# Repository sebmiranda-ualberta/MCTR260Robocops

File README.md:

# MCTR 260 Robocops
The GitHub repository for the Robocops! We are Group 10 in the MCTR 260 course on Mechatronics Design at the University of Alberta.

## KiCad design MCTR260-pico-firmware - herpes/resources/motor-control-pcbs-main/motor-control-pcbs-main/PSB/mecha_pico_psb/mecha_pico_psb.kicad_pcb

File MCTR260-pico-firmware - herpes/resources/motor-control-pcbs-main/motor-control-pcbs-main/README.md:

# MechaPico

This repository contains the KiCad project files
and component datasheets for the MechaPico Motor Control Board (MCB),
and Power Supply Board (PSB); developed by Stephine Yearley under
the guidance of Dr. Steven Knudsen at the University of Alberta.

TODO - Flesh out the README as development progresses

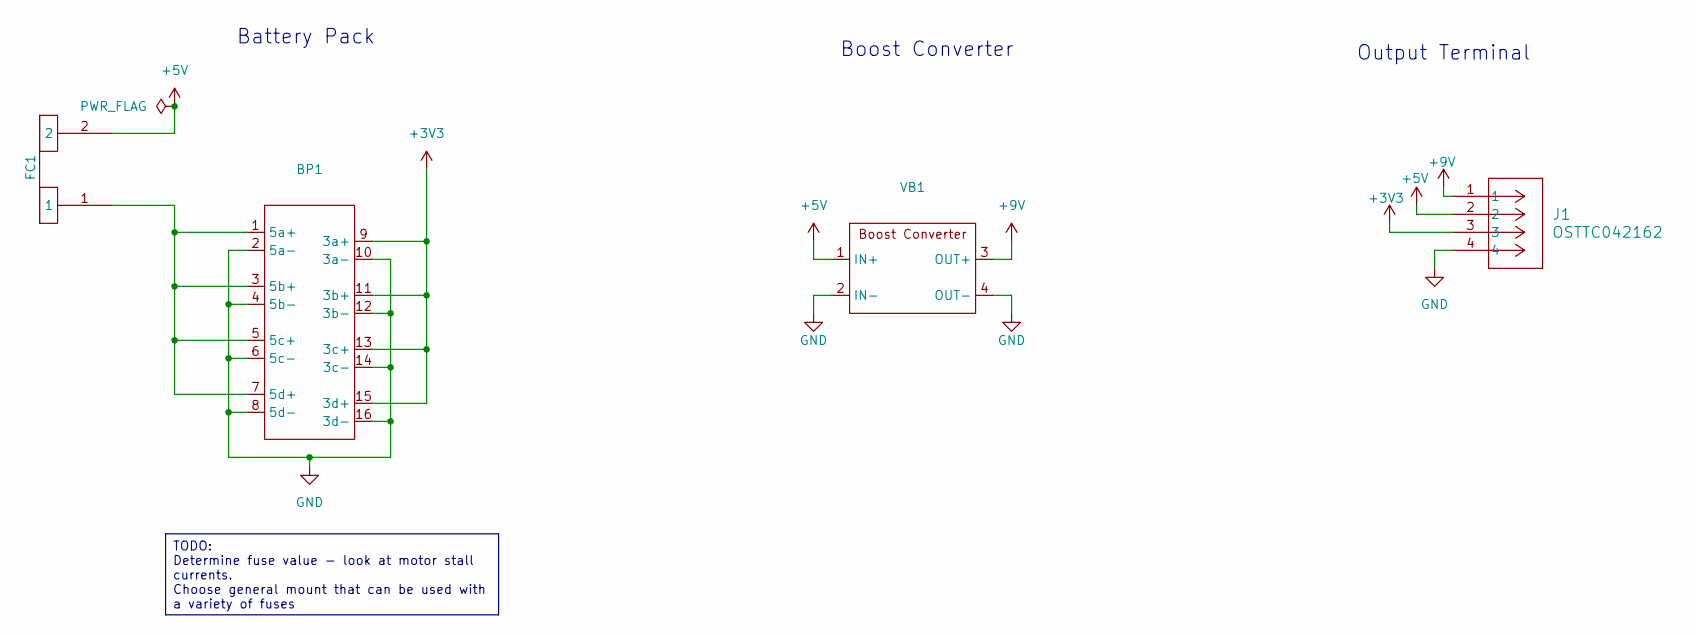
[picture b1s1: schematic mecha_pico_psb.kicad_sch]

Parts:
BP1: DIYmore_BatPak
FC1: FuseClip
J1: OSTTC042162; CONN_OSTTC042162_OST
VB1: VoltageBooster

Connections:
+3V3: BP1.9 (3a+), BP1.11 (3b+), BP1.13 (3c+), BP1.15 (3d+), J1.3
+5V: FC1.2, J1.2, VB1.1 (IN+)
+9V: J1.1, VB1.3 (OUT+)
GND: BP1.2 (5a-), BP1.4 (5b-), BP1.6 (5c-), BP1.8 (5d-), BP1.10 (3a-), BP1.12 (3b-), BP1.14 (3c-), BP1.16 (3d-), J1.4, VB1.2 (IN-), VB1.4 (OUT-)
unnamed: BP1.1 (5a+), BP1.3 (5b+), BP1.5 (5c+), BP1.7 (5d+), FC1.1

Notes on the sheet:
Output Terminal
Battery Pack
Boost Converter
TODO: Determine fuse value - look at motor stall currents. Choose general mount that can be used with a variety of fuses

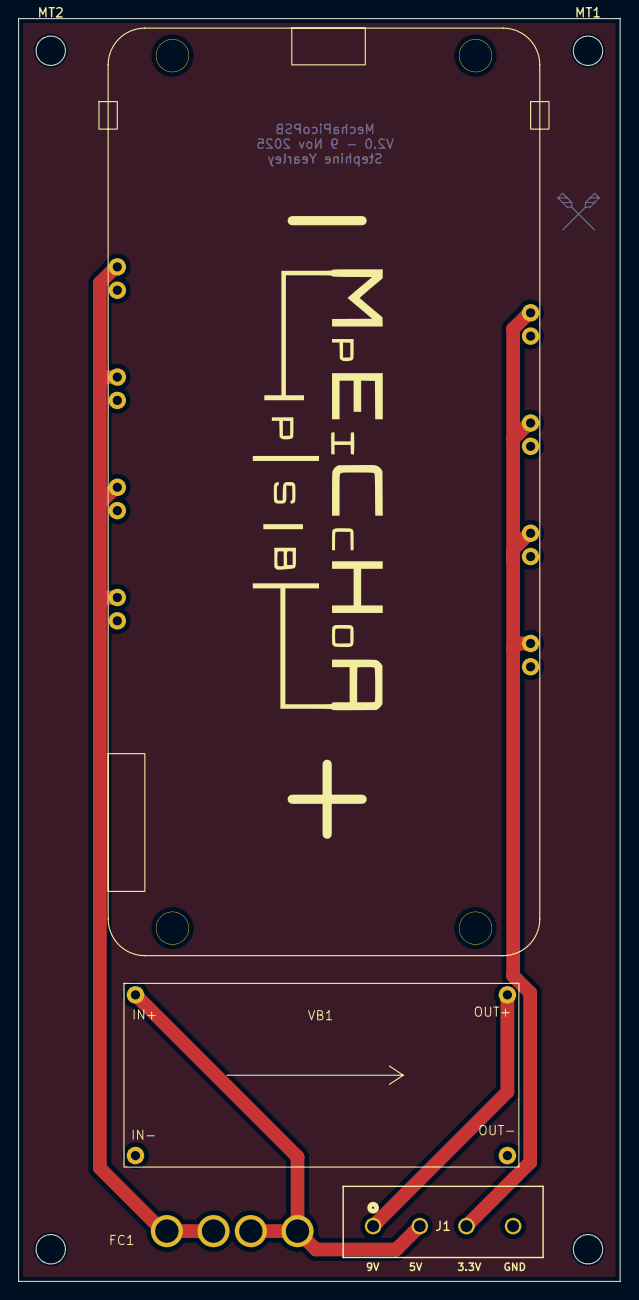
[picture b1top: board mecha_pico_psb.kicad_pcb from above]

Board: 2 copper layers, 65.5 x 137.5 mm, 8 parts (0 on the bottom side), 5 nets.

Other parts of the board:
MT1, MT2, MT3, MT4: MountingHole_3.2mm_M3

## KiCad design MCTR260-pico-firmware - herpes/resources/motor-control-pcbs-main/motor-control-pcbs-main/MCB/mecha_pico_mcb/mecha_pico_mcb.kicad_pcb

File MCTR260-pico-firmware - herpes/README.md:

# Raspberry Pi Pico W Robot Firmware

## What This Firmware Does

This firmware turns a Raspberry Pi Pico W into a **wireless robot controller**. You connect to it with a phone app over Bluetooth, and it translates your joystick movements into motor commands. It supports both DC motors (like the ones in toy cars) and stepper motors (precise motors that move in discrete steps), and it handles all the real-time control, safety, and communication automatically.

**In one sentence:** Phone app → Bluetooth → Pico W → motor drivers → wheels spin.

> [!IMPORTANT]
> **Hardware Platform:** This project is built around the **MECHA PICO** expansion board, a custom PCB designed for the MCTR 260 term project at the University of Alberta. All documentation, pin assignments, wiring diagrams, and code examples assume this specific board. If you are building from a bare Pico W, refer to the [Wiring Guide](doc/user_guide_documentation/WIRING_GUIDE.md) for the full connection list.

---

## How It Works

When you push the joystick in the Flutter app, here is what happens:

1. **App sends a JSON command** over Bluetooth Low Energy (BLE) to the Pico W
2. **Pico W parses the JSON** and extracts joystick position (x, y, rotation)
3. **Kinematics math runs** to convert your joystick input into 4 individual wheel speeds
4. **Motor drivers receive signals** (PWM for DC motors, step pulses for steppers)
5. **Safety watchdog monitors** the connection and stops everything if your phone disconnects

The Pico W has **two processor cores**. Core 0 handles Bluetooth and decision-making. Core 1 handles real-time stepper motor pulses. This separation ensures that Bluetooth processing never causes motor stuttering, and motor timing never blocks your Bluetooth connection.

---

## What You Need

### Hardware

| Component | Purpose | Notes |
|-----------|---------|-------|
| Raspberry Pi Pico W | The microcontroller brain | Must be the **W** variant (has Bluetooth) |
| Motor driver board(s) | Converts logic signals to motor power | See [Supported Motor Drivers](#supported-motor-drivers) below |
| Motors (up to 5 stepper + 2 DC) | Stepper and/or DC, depending on your build | Drive motors should be the same type |
| Power supply | Battery or bench supply | Voltage depends on your motors |
| USB cable | For uploading firmware and serial debugging | Micro-USB for Pico W |

### Software

| Tool | Purpose | Where to Get It |
|------|---------|-----------------|
| VS Code | Code editor | [code.visualstudio.com](https://code.visualstudio.com/) |
| PlatformIO extension | Builds and uploads firmware | Install from VS Code Extensions tab |
| RC Controller app | Phone app to drive the robot | Provided separately (Flutter) |

---

## Quick Start

> [!TIP]
> If this is your first time, read [GETTING_STARTED.md](doc/user_guide_documentation/GETTING_STARTED.md) for a detailed walkthrough of every step.

1. Open this project folder in VS Code with PlatformIO installed
2. Edit `src/project_config.h` to set your robot's name, PIN, and motor driver type
3. Build and upload:
   ```
   pio run -t upload
   ```
4. Open serial monitor to verify boot:
   ```
   pio run -t monitor
   ```
5. Open the Flutter app → scan for your robot → enter the PIN → drive!

---

## Project Structure

```
├── platformio.ini          # Build configuration (do not edit unless adding libraries)
├── src/
│   ├── project_config.h    # ← YOUR SETTINGS (device name, PIN, motor type, GPIO pins)
│   ├── main.cpp            # Entry point for both cores
│   ├── core/               # BLE communication, command parsing, motor management, safety
│   ├── drivers/            # Hardware drivers (MCP23017, kinematics math)
│   └── profiles/           # Motion profiles (mecanum, auxiliary motors)
├── doc/                    # Student documentation
├── resources/              # PCB design files and datasheets
├── LICENSE                 # MIT License
└── README.md               # You are here
```

**Key file:** `src/project_config.h` is the **only file** you need to edit for basic setup. Everything else is internal firmware code.

---

## Supported Motor Drivers

### DC Motor Drivers

| Driver | Motors per Chip | Pico Pins per Motor | Max Current | Best For |
|--------|:--------------:|:-------------------:|:-----------:|----------|
| DRV8871 | 1 | 2 PWM | 3.6A | High-power single motors |
| DRV8833 | 2 | 2 PWM | 1.5A | Small to medium robots |
| L298N | 2 | 3 (2 dir + 1 PWM) | 2A | Easy to source, common in kits |

### Stepper Motor Drivers

| Driver | Max Microsteps | Max Current | Noise Level | Best For |
|--------|:--------------:|:-----------:|:-----------:|----------|
| TMC2209 | 1/256 (internal) | 2.8A | Very quiet | Precision, quiet operation |
| A4988 | 1/16 | 2A | Moderate | Budget builds |
| DRV8825 | 1/32 | 2.5A | Moderate | Mid-range, higher resolution |

> [!IMPORTANT]
> You must uncomment **exactly one** motor driver in `project_config.h`. Uncommenting more than one causes a compile error.

### Which Driver Should I Pick?

- **Using the MechaPico MCB (custom PCB)?** → Use `TMC2209` (it is pre-wired on the board)
- **Building from scratch with DC motors?** → Start with `DRV8833` (cheap, 2 motors per chip)
- **Need maximum torque?** → Use `DRV8871` (highest current per channel)
- **Using stepper motors on a breadboard?** → Start with `A4988` (widely available, simple wiring)

---

## BLE Pairing

1. Power on your robot (plug in USB or connect battery)
2. Open the Flutter RC Controller app
3. Tap **Scan** on the connection screen
4. Select your robot's name from the list (e.g., `TimberBot_RC`)
5. Enter the 6-digit PIN (default: `123456`, set in `project_config.h`)
6. You are connected. Push the joystick to drive.

> [!TIP]
> **Robot not appearing in the scan list?** Include one of these keywords in your device name so the app shows it at the top: `robot`, `rc`, `pico`, `mecanum`, `tank`, `meca`, `controller`.

> [!WARNING]
> If you change `DEVICE_NAME` or `BLE_PASSKEY` in the firmware, your phone will see a "new device." Delete the old pairing from your phone's Bluetooth settings and re-pair.

---

## Feature Status

| Feature | Status | Notes |
|---------|:------:|-------|
| BLE Control | ✅ | BTstack GATT server with passkey pairing |
| DC Motors (M1-M4) | ✅ | DRV8871, DRV8833, L298N drivers via Pico GPIO |
| Stepper Motors (M1-M4) | ✅ | TMC2209, A4988, DRV8825 via MCP23017 |
| Motor 5 (Spare Stepper) | ✅ | Config-only: runs on Core 1 with full acceleration |
| DC Motors 3-4 (Auxiliary) | ✅ | Config-only: on/off direction via MCP23017 U6_2 |
| Mecanum Kinematics | ✅ | 4-wheel omnidirectional drive |
| Safety Watchdog | ✅ | Auto-stop on lost connection |
| Dual-Core | ✅ | Core 0: BLE/logic, Core 1: stepper pulses |
| Telemetry | ✅ | BLE notify characteristic |
| Encoders | ⏳ | Planned |
| PID Control | ⏳ | Planned |

---

## Where to Go Next

Read these documents **in order**. Each builds on the previous one:

| # | Document | Purpose | When to Read |
|:-:|----------|---------|-------------|
| 1 | **You are here** (README) | Orientation and overview | Right now |
| 2 | [GETTING_STARTED](doc/user_guide_documentation/GETTING_STARTED.md) | Build, upload, and pair for the first time | First time setting up |
| 3 | [CONFIGURATION_REFERENCE](doc/user_guide_documentation/CONFIGURATION_REFERENCE.md) | Every setting in `project_config.h` explained | Customizing your robot |
| 4 | [WIRING_GUIDE](doc/user_guide_documentation/WIRING_GUIDE.md) | Physical connections: Pico, MCP23017, drivers, motors | Wiring or debugging hardware |
| 5 | [ARCHITECTURE](doc/user_guide_documentation/ARCHITECTURE.md) | How the firmware works internally (dual-core, BLE, safety) | Understanding the code |
| 6 | [BLE_PROTOCOL](doc/user_guide_documentation/BLE_PROTOCOL.md) | BLE service/characteristic details, JSON schema, connection flow | Deep-dive into communication |
| 7 | [EXTENDING_THE_FIRMWARE](doc/user_guide_documentation/EXTENDING_THE_FIRMWARE.md) | Add your own motors, sensors, and profiles | **Term project: adding mission-specific code** |
| 8 | [TROUBLESHOOTING](doc/user_guide_documentation/TROUBLESHOOTING.md) | Common problems and solutions | When something breaks |

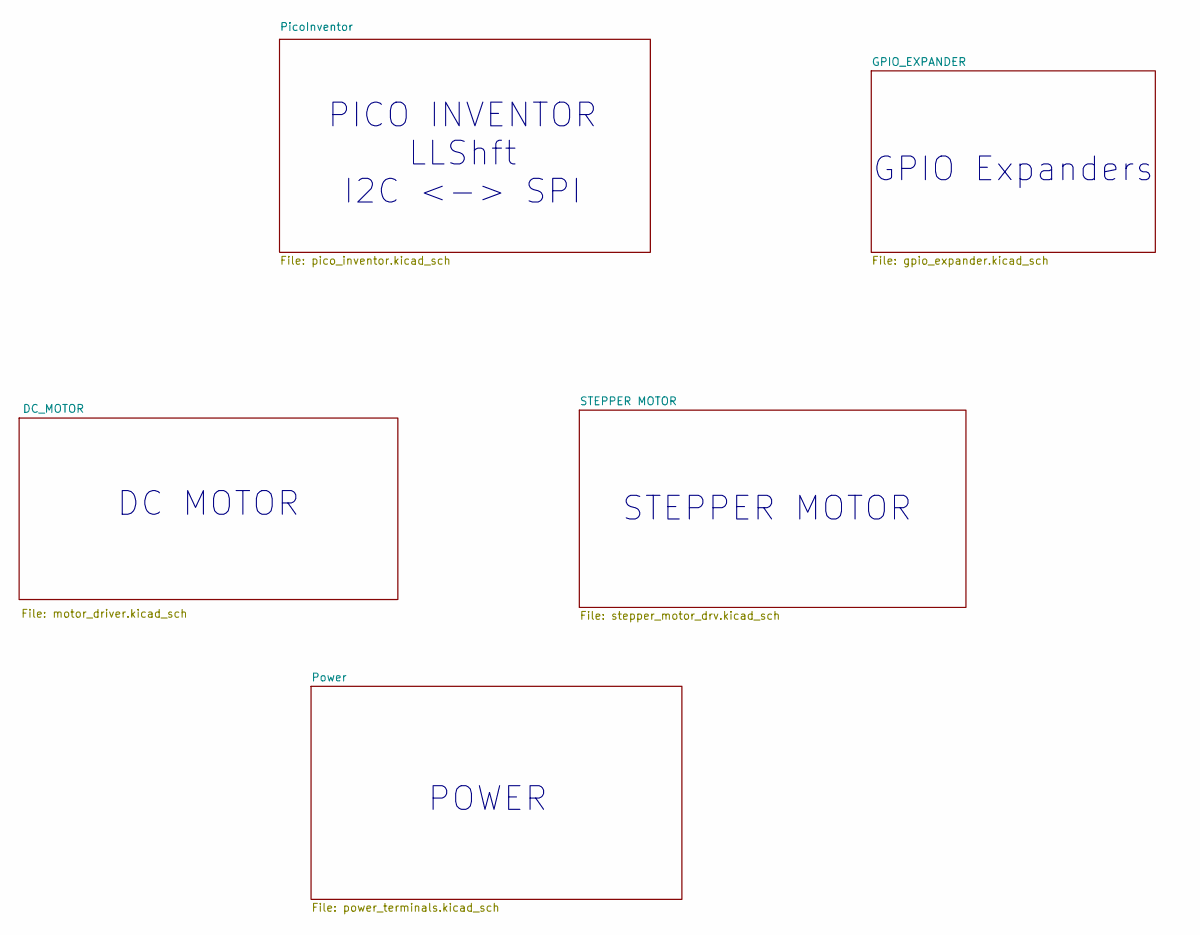
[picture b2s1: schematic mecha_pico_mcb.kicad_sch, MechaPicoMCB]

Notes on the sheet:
DC MOTOR
GPIO Expanders
STEPPER MOTOR
POWER
PICO INVENTOR LLShft I2C <-> SPI

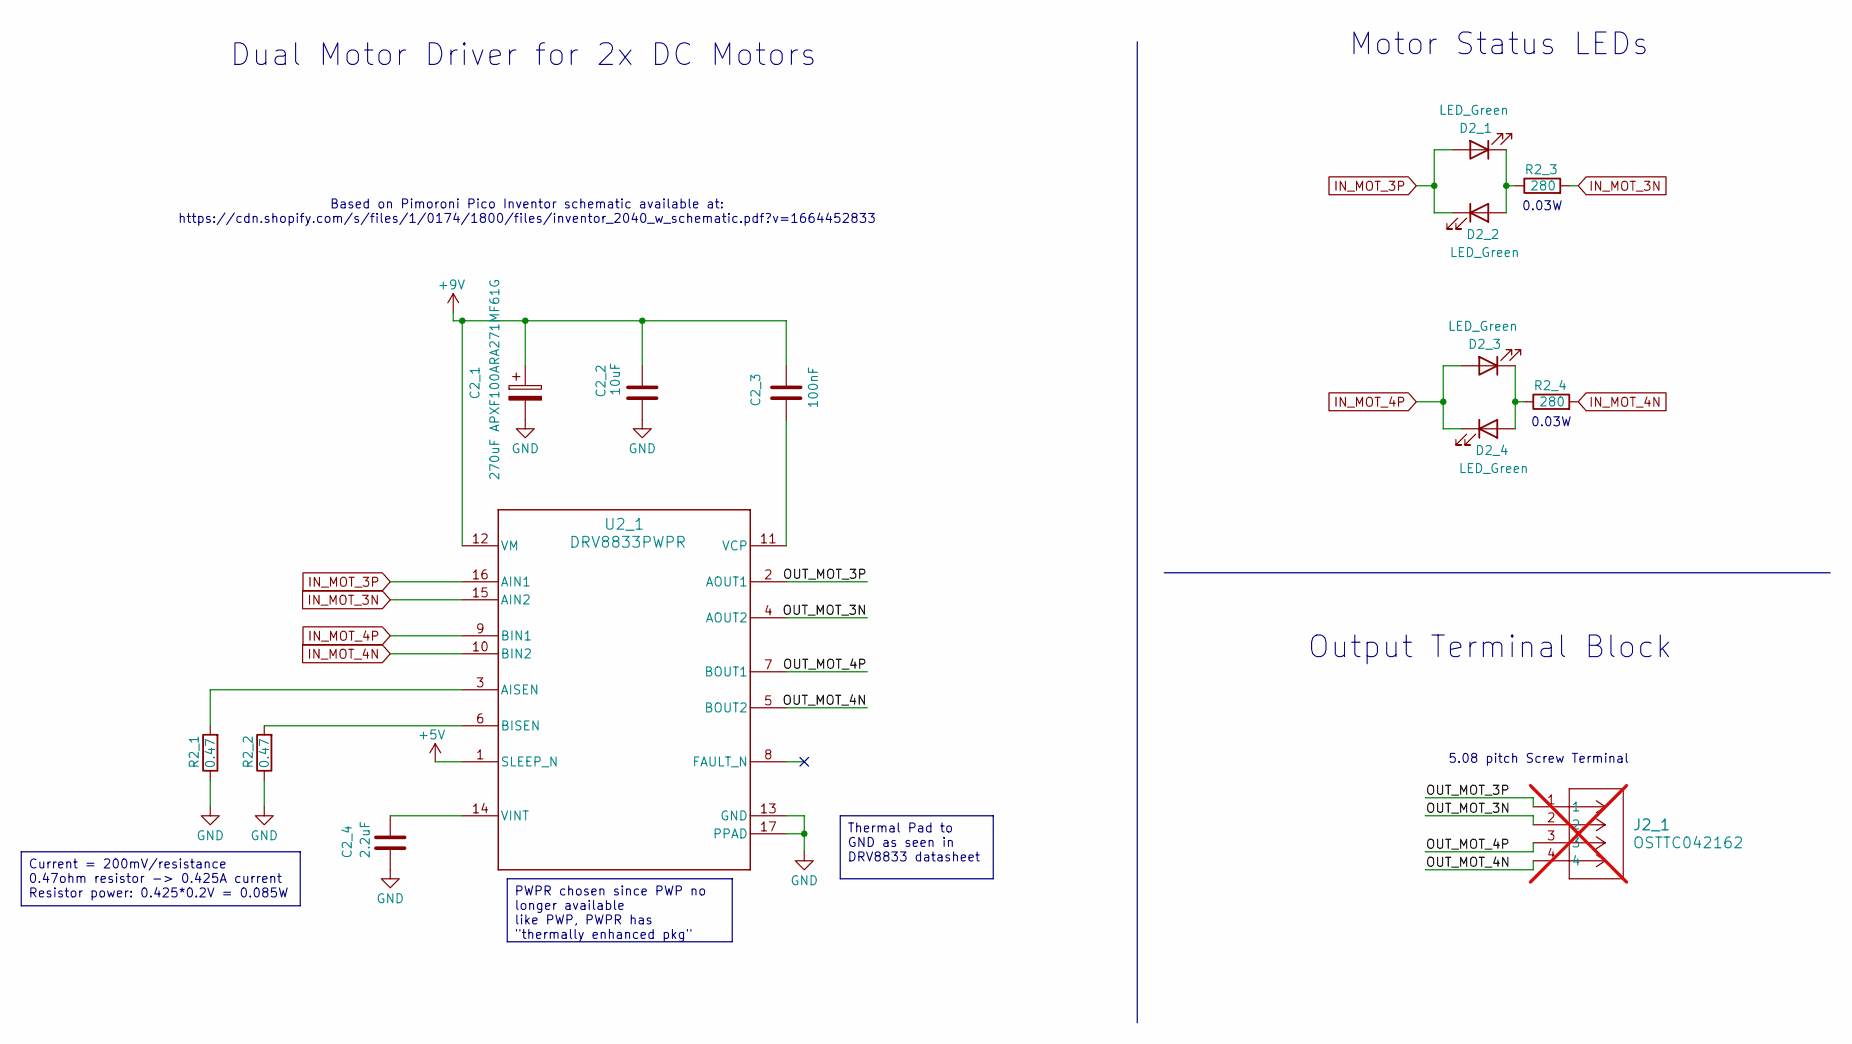
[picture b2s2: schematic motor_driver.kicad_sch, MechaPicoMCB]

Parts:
C2_1: 270uF APXF100ARA271MF61G; CP_Elec_6.3x5.7; MPN APXF100ARA271MF61G
C2_2: 10uF; C_0603_1608Metric_Pad1.08x0.95mm_HandSolder; MPN GRM188R61E106KA73D
C2_3: 100nF; C_0603_1608Metric_Pad1.08x0.95mm_HandSolder; MPN C0603C104K5RACTU
C2_4: 2.2uF; C_0603_1608Metric_Pad1.08x0.95mm_HandSolder; MPN CL10A225KO8NNNC
D2_1, D2_2, D2_3, D2_4: LED_Green; C_1206_3216Metric_Pad1.33x1.80mm_HandSolder; MPN LTST-C150GKT
J2_1: OSTTC042162; CONN_OSTTC042162_OST; MPN OSTTC042162; not fitted
R2_1, R2_2: 0.47; R_0603_1608Metric_Pad0.98x0.95mm_HandSolder; MPN ERJ-3BQJR47V
R2_3, R2_4: 280; R_0603_1608Metric_Pad0.98x0.95mm_HandSolder; MPN RK73H1JTTD2800F
U2_1: DRV8833PWPR; PWP0016C_M; MPN DRV8833PWPR

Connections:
+5V: U2_1.1 (SLEEP_N); also elsewhere on the board
+9V: C2_1.1, C2_2.1, C2_3.1, U2_1.12 (VM); also elsewhere on the board
/DC_MOTOR/OUT_MOT_3N: J2_1.2, U2_1.4 (AOUT2)
/DC_MOTOR/OUT_MOT_3P: J2_1.1, U2_1.2 (AOUT1)
/DC_MOTOR/OUT_MOT_4N: J2_1.4, U2_1.5 (BOUT2)
/DC_MOTOR/OUT_MOT_4P: J2_1.3, U2_1.7 (BOUT1)
GND: C2_1.2, C2_2.2, C2_4.2, R2_1.1, R2_2.1, U2_1.13 (GND), U2_1.17 (PPAD); also elsewhere on the board
IN_MOT_3N: R2_3.2, U2_1.15 (AIN2); also elsewhere on the board
IN_MOT_3P: D2_1.2 (A), D2_2.1 (K), U2_1.16 (AIN1); also elsewhere on the board
IN_MOT_4N: R2_4.2, U2_1.10 (BIN2); also elsewhere on the board
IN_MOT_4P: D2_3.2 (A), D2_4.1 (K), U2_1.9 (BIN1); also elsewhere on the board
unnamed: D2_1.1 (K), D2_2.2 (A), R2_3.1
unnamed: D2_3.1 (K), D2_4.2 (A), R2_4.1
unnamed: R2_1.2, U2_1.3 (AISEN)
unnamed: R2_2.2, U2_1.6 (BISEN)
unnamed: C2_3.2, U2_1.11 (VCP)
unnamed: C2_4.1, U2_1.14 (VINT)

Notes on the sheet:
0.03W
Motor Status LEDs
Based on Pimoroni Pico Inventor schematic available at: https://cdn.shopify.com/s/files/1/0174/1800/files/inventor_2040_w_schematic.pdf?v=1664452833
Output Terminal Block
Dual Motor Driver for 2x DC Motors
5.08 pitch Screw Terminal
Current = 200mV/resistance 0.47ohm resistor -> 0.425A current Resistor power: 0.425*0.2V = 0.085W
Thermal Pad to GND as seen in DRV8833 datasheet
PWPR chosen since PWP no longer available like PWP, PWPR has "thermally enhanced pkg"

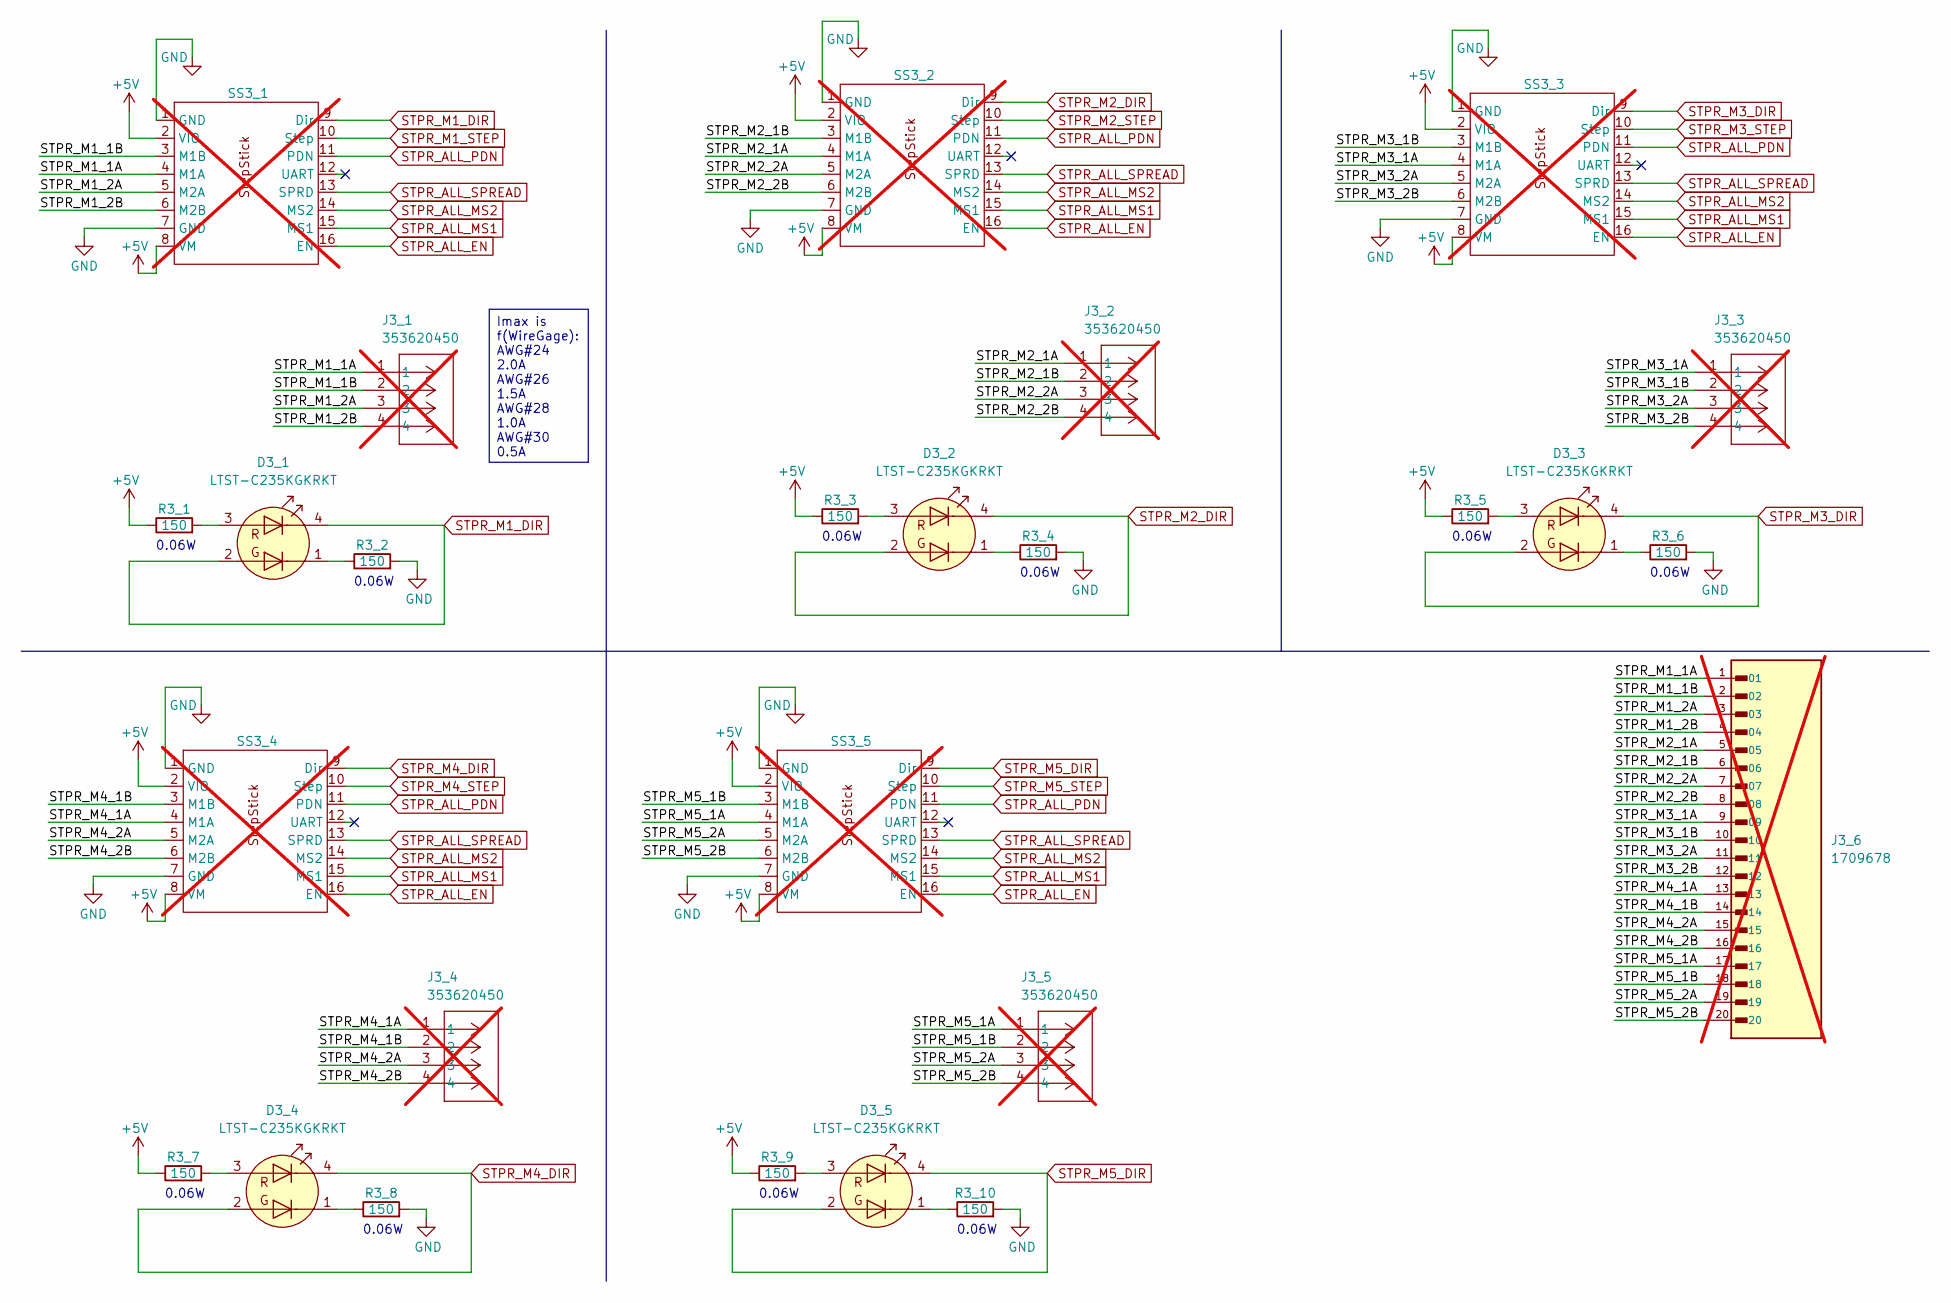
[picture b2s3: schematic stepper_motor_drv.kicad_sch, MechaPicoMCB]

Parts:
D3_1, D3_2, D3_3, D3_4, D3_5: LTST-C235KGKRKT; LTST-C235KGKRKT_LTO-L; MPN LTST-C235KGKRKT
J3_1, J3_2, J3_3, J3_4, J3_5: 353620450; CON_353620450; MPN 0353620450; not fitted
J3_6: 1709678; PHOENIX_1709678; PARTREV 02.08.2023; not fitted
R3_1, R3_2, R3_3, R3_4, R3_5, R3_6, R3_7, R3_8, R3_9, R3_10: 150; R_0603_1608Metric_Pad0.98x0.95mm_HandSolder; MPN RK73B1JTTD151J
SS3_1, SS3_2, SS3_3, SS3_4, SS3_5: StepStick; MPN TMC2209SILENTSTEPSTICK; not fitted

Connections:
+5V: R3_1.1, R3_3.1, R3_5.1, R3_7.1, R3_9.1, SS3_1.2 (VIO), SS3_1.8 (VM), SS3_2.2 (VIO), SS3_2.8 (VM), SS3_3.2 (VIO), SS3_3.8 (VM), SS3_4.2 (VIO), SS3_4.8 (VM), SS3_5.2 (VIO), SS3_5.8 (VM); also elsewhere on the board
/STEPPER MOTOR/STPR_M1_1A: J3_1.1, J3_6.1, SS3_1.4 (M1A)
/STEPPER MOTOR/STPR_M1_1B: J3_1.2, J3_6.2, SS3_1.3 (M1B)
/STEPPER MOTOR/STPR_M1_2A: J3_1.3, J3_6.3, SS3_1.5 (M2A)
/STEPPER MOTOR/STPR_M1_2B: J3_1.4, J3_6.4, SS3_1.6 (M2B)
/STEPPER MOTOR/STPR_M2_1A: J3_2.1, J3_6.5, SS3_2.4 (M1A)
/STEPPER MOTOR/STPR_M2_1B: J3_2.2, J3_6.6, SS3_2.3 (M1B)
/STEPPER MOTOR/STPR_M2_2A: J3_2.3, J3_6.7, SS3_2.5 (M2A)
/STEPPER MOTOR/STPR_M2_2B: J3_2.4, J3_6.8, SS3_2.6 (M2B)
/STEPPER MOTOR/STPR_M3_1A: J3_3.1, J3_6.9, SS3_3.4 (M1A)
/STEPPER MOTOR/STPR_M3_1B: J3_3.2, J3_6.10, SS3_3.3 (M1B)
/STEPPER MOTOR/STPR_M3_2A: J3_3.3, J3_6.11, SS3_3.5 (M2A)
/STEPPER MOTOR/STPR_M3_2B: J3_3.4, J3_6.12, SS3_3.6 (M2B)
/STEPPER MOTOR/STPR_M4_1A: J3_4.1, J3_6.13, SS3_4.4 (M1A)
/STEPPER MOTOR/STPR_M4_1B: J3_4.2, J3_6.14, SS3_4.3 (M1B)
/STEPPER MOTOR/STPR_M4_2A: J3_4.3, J3_6.15, SS3_4.5 (M2A)
/STEPPER MOTOR/STPR_M4_2B: J3_4.4, J3_6.16, SS3_4.6 (M2B)
/STEPPER MOTOR/STPR_M5_1A: J3_5.1, J3_6.17, SS3_5.4 (M1A)
/STEPPER MOTOR/STPR_M5_1B: J3_5.2, J3_6.18, SS3_5.3 (M1B)
/STEPPER MOTOR/STPR_M5_2A: J3_5.3, J3_6.19, SS3_5.5 (M2A)
/STEPPER MOTOR/STPR_M5_2B: J3_5.4, J3_6.20, SS3_5.6 (M2B)
GND: R3_2.2, R3_4.2, R3_6.2, R3_8.2, R3_10.2, SS3_1.1 (GND), SS3_1.7 (GND), SS3_2.1 (GND), SS3_2.7 (GND), SS3_3.1 (GND), SS3_3.7 (GND), SS3_4.1 (GND), SS3_4.7 (GND), SS3_5.1 (GND), SS3_5.7 (GND); also elsewhere on the board
unnamed: D3_1.3 (A1), R3_1.2
unnamed: D3_1.1 (K2), R3_2.1
unnamed: D3_2.3 (A1), R3_3.2
unnamed: D3_2.1 (K2), R3_4.1
unnamed: D3_3.3 (A1), R3_5.2
unnamed: D3_3.1 (K2), R3_6.1
unnamed: D3_4.3 (A1), R3_7.2
unnamed: D3_4.1 (K2), R3_8.1
unnamed: D3_5.3 (A1), R3_9.2
unnamed: D3_5.1 (K2), R3_10.1
STPR_ALL_EN: SS3_1.16 (EN), SS3_2.16 (EN), SS3_3.16 (EN), SS3_4.16 (EN), SS3_5.16 (EN); also elsewhere on the board
STPR_ALL_MS1: SS3_1.15 (MS1), SS3_2.15 (MS1), SS3_3.15 (MS1), SS3_4.15 (MS1), SS3_5.15 (MS1); also elsewhere on the board
STPR_ALL_MS2: SS3_1.14 (MS2), SS3_2.14 (MS2), SS3_3.14 (MS2), SS3_4.14 (MS2), SS3_5.14 (MS2); also elsewhere on the board
STPR_ALL_PDN: SS3_1.11 (PDN), SS3_2.11 (PDN), SS3_3.11 (PDN), SS3_4.11 (PDN), SS3_5.11 (PDN); also elsewhere on the board
STPR_ALL_SPREAD: SS3_1.13 (SPRD), SS3_2.13 (SPRD), SS3_3.13 (SPRD), SS3_4.13 (SPRD), SS3_5.13 (SPRD); also elsewhere on the board
STPR_M1_DIR: D3_1.2 (A2), D3_1.4 (K1), SS3_1.9 (Dir); also elsewhere on the board
STPR_M1_STEP: SS3_1.10 (Step); also elsewhere on the board
STPR_M2_DIR: D3_2.2 (A2), D3_2.4 (K1), SS3_2.9 (Dir); also elsewhere on the board
STPR_M2_STEP: SS3_2.10 (Step); also elsewhere on the board
STPR_M3_DIR: D3_3.2 (A2), D3_3.4 (K1), SS3_3.9 (Dir); also elsewhere on the board
STPR_M3_STEP: SS3_3.10 (Step); also elsewhere on the board
STPR_M4_DIR: D3_4.2 (A2), D3_4.4 (K1), SS3_4.9 (Dir); also elsewhere on the board
STPR_M4_STEP: SS3_4.10 (Step); also elsewhere on the board
STPR_M5_DIR: D3_5.2 (A2), D3_5.4 (K1), SS3_5.9 (Dir); also elsewhere on the board
STPR_M5_STEP: SS3_5.10 (Step); also elsewhere on the board

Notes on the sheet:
0.06W
Imax is f(WireGage): AWG#24 2.0A AWG#26 1.5A AWG#28 1.0A AWG#30 0.5A

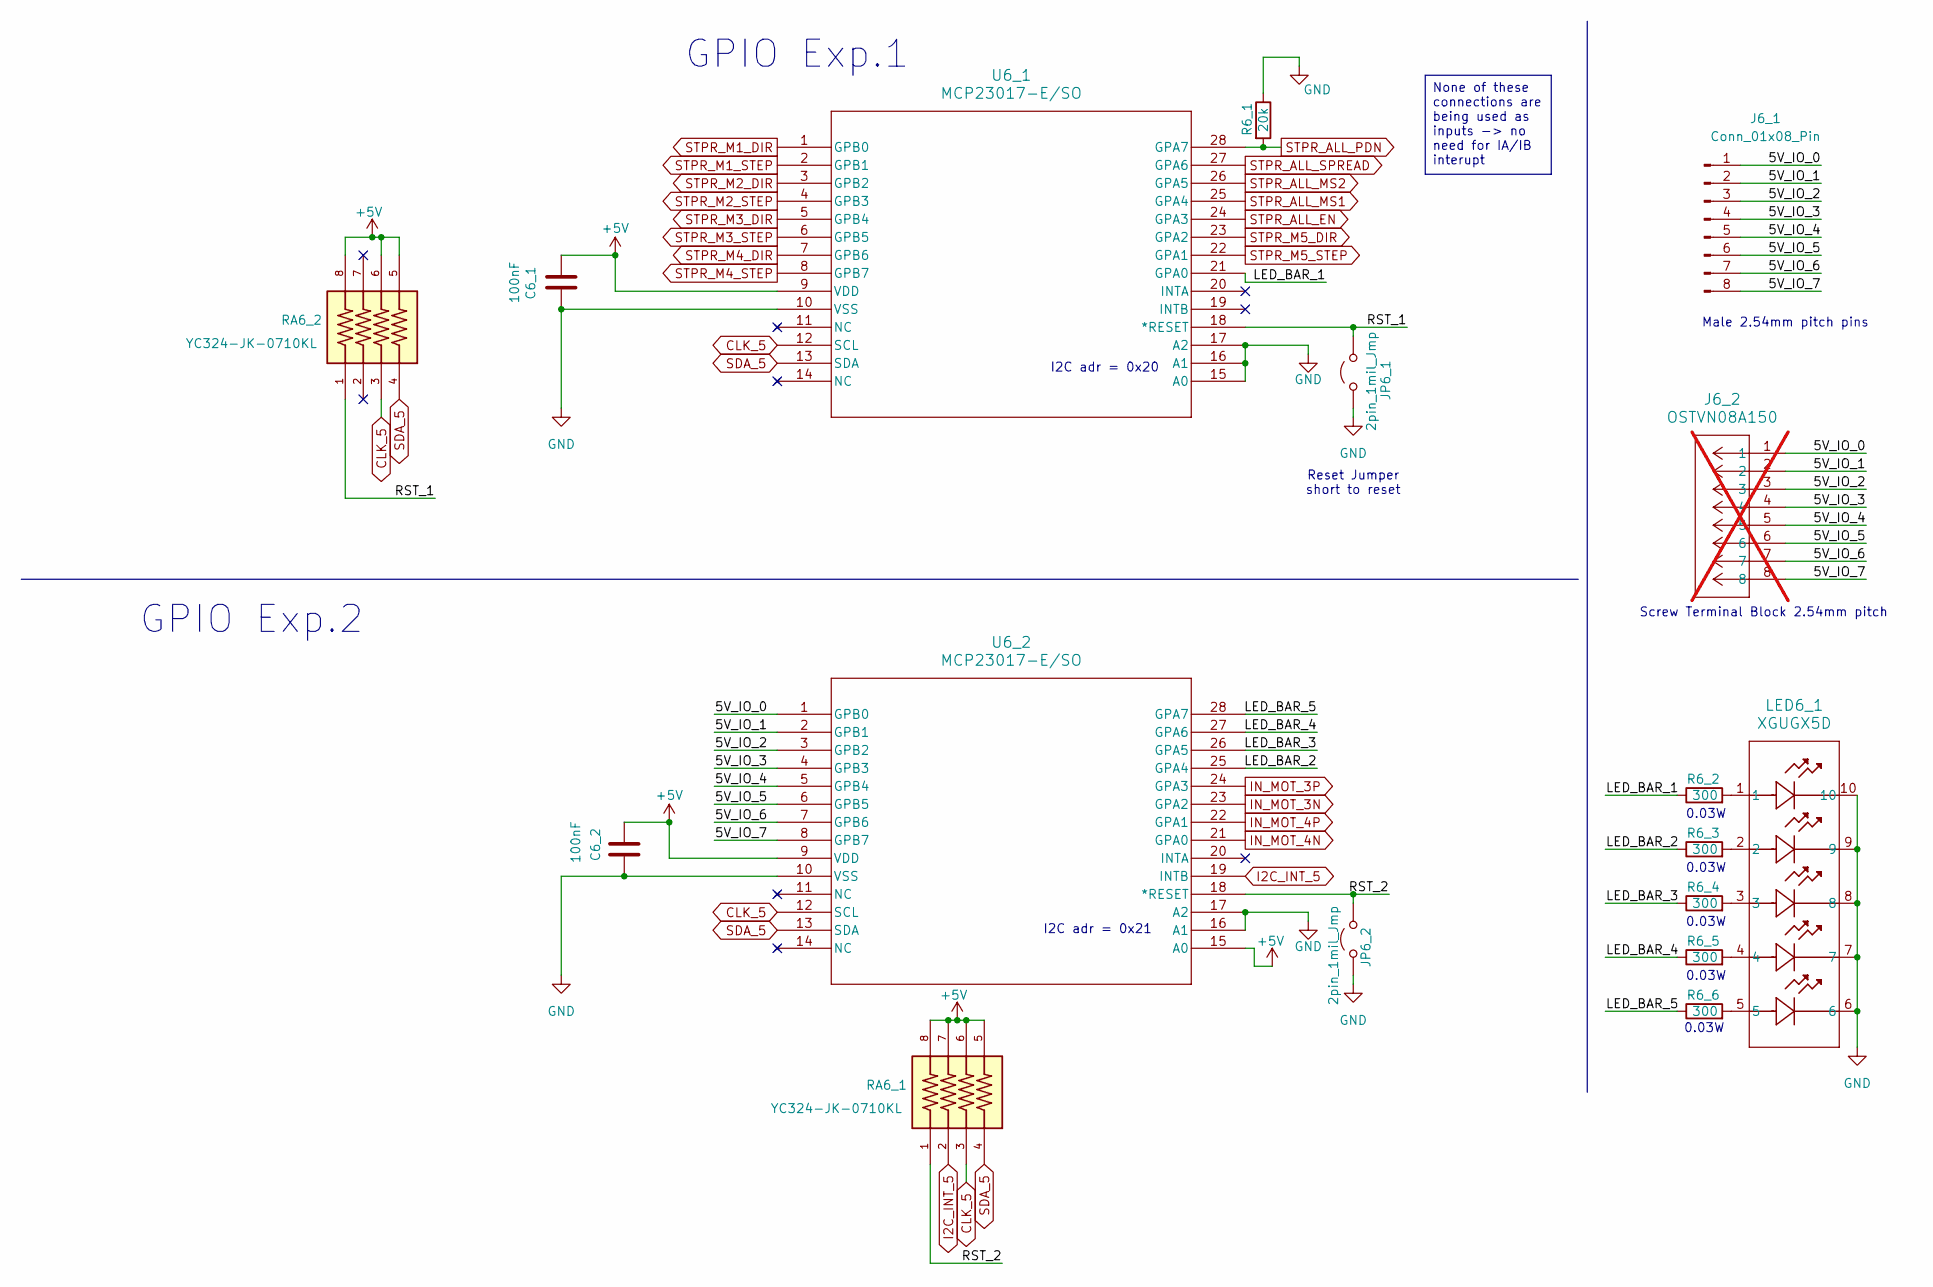
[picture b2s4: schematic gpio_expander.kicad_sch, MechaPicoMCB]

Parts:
C6_1, C6_2: 100nF; C_0603_1608Metric_Pad1.08x0.95mm_HandSolder; MPN C0603C104K5RACTU
J6_1: Conn_01x08_Pin; PinSocket_1x08_P2.54mm_Vertical; MPN PPTC081LFBN-RC
J6_2: OSTVN08A150; CONN_OSTVN08A150_OST; MPN OSTVN08A150; not fitted
JP6_1, JP6_2: 2pin_1mil_Jmp; PinHeader_1x02_P2.54mm_Vertical; PartNote MaleHeader_2x1_1mil_&_header_con
LED6_1: XGUGX5D; RLA10_XGUGX5D_SLD; MPN XGUGX5D
R6_1: 20k; R_0603_1608Metric_Pad0.98x0.95mm_HandSolder; MPN RC0603FR-0720KL
R6_2, R6_3, R6_4, R6_5, R6_6: 300; R_0603_1608Metric_Pad0.98x0.95mm_HandSolder; MPN RMCF0603JT300R
RA6_1, RA6_2: YC324-JK-0710KL; RES_YC324_5P08X3P2_YAG-M; PARTREV V.9
U6_1, U6_2: MCP23017-E/SO; SOIC-28W_7.5x17.9mm_P1.27mm; MPN MCP23017-E/SO

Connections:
+5V: C6_1.1, C6_2.1, RA6_1.5, RA6_1.6, RA6_1.7, RA6_1.8, RA6_2.5, RA6_2.6, RA6_2.8, U6_1.9 (VDD), U6_2.9 (VDD), U6_2.15 (A0); also elsewhere on the board
/GPIO_EXPANDER/5V_IO_0: J6_1.1, J6_2.1, U6_2.1 (GPB0)
/GPIO_EXPANDER/5V_IO_1: J6_1.2, J6_2.2, U6_2.2 (GPB1)
/GPIO_EXPANDER/5V_IO_2: J6_1.3, J6_2.3, U6_2.3 (GPB2)
/GPIO_EXPANDER/5V_IO_3: J6_1.4, J6_2.4, U6_2.4 (GPB3)
/GPIO_EXPANDER/5V_IO_4: J6_1.5, J6_2.5, U6_2.5 (GPB4)
/GPIO_EXPANDER/5V_IO_5: J6_1.6, J6_2.6, U6_2.6 (GPB5)
/GPIO_EXPANDER/5V_IO_6: J6_1.7, J6_2.7, U6_2.7 (GPB6)
/GPIO_EXPANDER/5V_IO_7: J6_1.8, J6_2.8, U6_2.8 (GPB7)
/GPIO_EXPANDER/LED_BAR_1: R6_2.1, U6_1.21 (GPA0)
/GPIO_EXPANDER/LED_BAR_2: R6_3.1, U6_2.25 (GPA4)
/GPIO_EXPANDER/LED_BAR_3: R6_4.1, U6_2.26 (GPA5)
/GPIO_EXPANDER/LED_BAR_4: R6_5.1, U6_2.27 (GPA6)
/GPIO_EXPANDER/LED_BAR_5: R6_6.1, U6_2.28 (GPA7)
/GPIO_EXPANDER/RST_1: JP6_1.2 (B), RA6_2.1, U6_1.18 (*RESET)
/GPIO_EXPANDER/RST_2: JP6_2.2 (B), RA6_1.1, U6_2.18 (*RESET)
CLK_5: RA6_1.3, RA6_2.3, U6_1.12 (SCL), U6_2.12 (SCL); also elsewhere on the board
GND: C6_1.2, C6_2.2, JP6_1.1 (A), JP6_2.1 (A), LED6_1.6, LED6_1.7, LED6_1.8, LED6_1.9, LED6_1.10, R6_1.1, U6_1.10 (VSS), U6_1.15 (A0), U6_1.16 (A1), U6_1.17 (A2), U6_2.10 (VSS), U6_2.16 (A1), U6_2.17 (A2); also elsewhere on the board
I2C_INT_5: RA6_1.2, U6_2.19 (INTB); also elsewhere on the board
IN_MOT_3N: U6_2.23 (GPA2); also elsewhere on the board
IN_MOT_3P: U6_2.24 (GPA3); also elsewhere on the board
IN_MOT_4N: U6_2.21 (GPA0); also elsewhere on the board
IN_MOT_4P: U6_2.22 (GPA1); also elsewhere on the board
unnamed: LED6_1.1, R6_2.2
unnamed: LED6_1.2, R6_3.2
unnamed: LED6_1.3, R6_4.2
unnamed: LED6_1.4, R6_5.2
unnamed: LED6_1.5, R6_6.2
SDA_5: RA6_1.4, RA6_2.4, U6_1.13 (SDA), U6_2.13 (SDA); also elsewhere on the board
STPR_ALL_EN: U6_1.24 (GPA3); also elsewhere on the board
STPR_ALL_MS1: U6_1.25 (GPA4); also elsewhere on the board
STPR_ALL_MS2: U6_1.26 (GPA5); also elsewhere on the board
STPR_ALL_PDN: R6_1.2, U6_1.28 (GPA7); also elsewhere on the board
STPR_ALL_SPREAD: U6_1.27 (GPA6); also elsewhere on the board
STPR_M1_DIR: U6_1.1 (GPB0); also elsewhere on the board
STPR_M1_STEP: U6_1.2 (GPB1); also elsewhere on the board
STPR_M2_DIR: U6_1.3 (GPB2); also elsewhere on the board
STPR_M2_STEP: U6_1.4 (GPB3); also elsewhere on the board
STPR_M3_DIR: U6_1.5 (GPB4); also elsewhere on the board
STPR_M3_STEP: U6_1.6 (GPB5); also elsewhere on the board
STPR_M4_DIR: U6_1.7 (GPB6); also elsewhere on the board
STPR_M4_STEP: U6_1.8 (GPB7); also elsewhere on the board
STPR_M5_DIR: U6_1.23 (GPA2); also elsewhere on the board
STPR_M5_STEP: U6_1.22 (GPA1); also elsewhere on the board

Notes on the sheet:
0.03W
Male 2.54mm pitch pins
GPIO Exp.2
GPIO Exp.1
Reset Jumper short to reset
I2C adr = 0x21
I2C adr = 0x20
Screw Terminal Block 2.54mm pitch
None of these connections are being used as inputs -> no need for IA/IB interupt

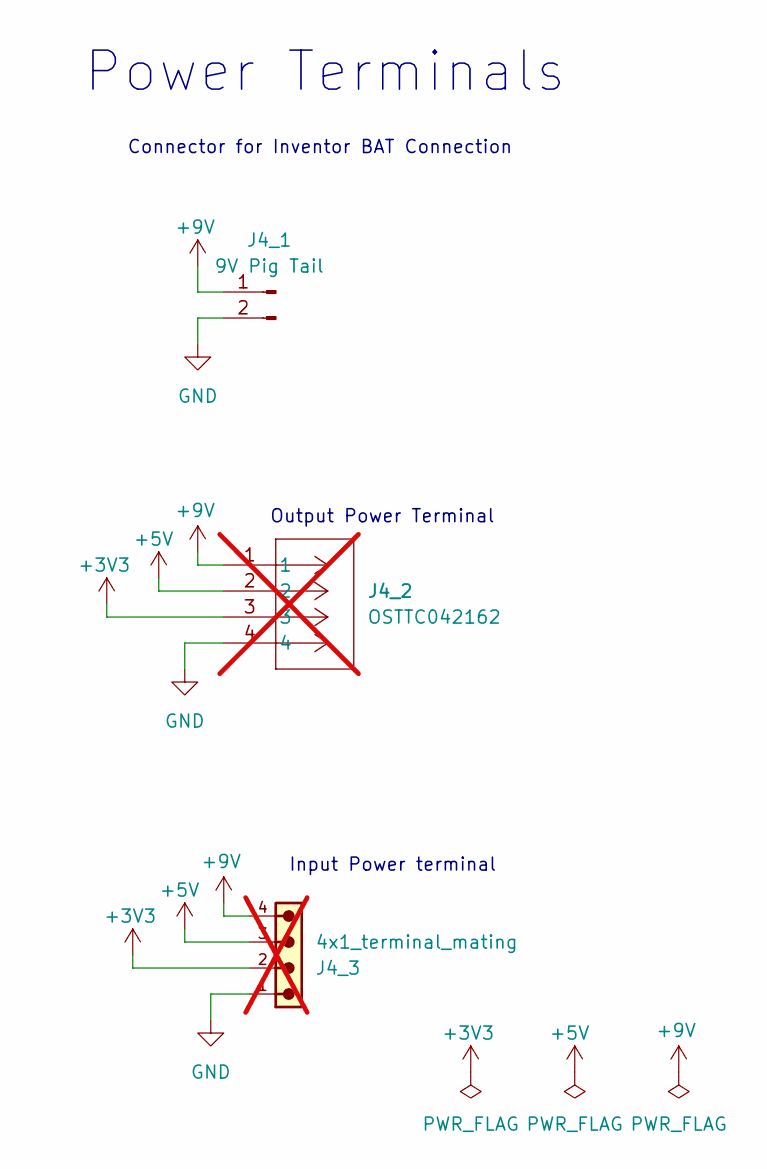
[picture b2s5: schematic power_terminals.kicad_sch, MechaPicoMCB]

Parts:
J4_1: 9V Pig Tail; PinHeader_1x02_P1.27mm_Vertical
J4_2: OSTTC042162; CONN_OSTTC042162_OST; MPN OSTTC042162; not fitted
J4_3: 4x1_terminal_mating; 691313510004; not fitted

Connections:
+3V3: J4_2.3, J4_3.2; also elsewhere on the board
+5V: J4_2.2, J4_3.3; also elsewhere on the board
+9V: J4_1.1, J4_2.1, J4_3.4; also elsewhere on the board
GND: J4_1.2, J4_2.4, J4_3.1; also elsewhere on the board

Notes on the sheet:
Power Terminals
Output Power Terminal
Input Power terminal
Connector for Inventor BAT Connection

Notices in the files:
MCTR260-pico-firmware - herpes/resources/motor-control-pcbs-main/motor-control-pcbs-main/MCB/mecha_pico_mcb/gpio_expander.kicad_sch:
License : CC BY-NC 4.0
